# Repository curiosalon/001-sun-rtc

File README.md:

# NVRAM/IDPROM Replacement for M48T59Y Real Time Clock

This project intends to design a timing and register compatible module
to replace the now obsoleted M48T59Y realtime clock chip used in
the following Sun Microsystems computers:

| WORKSTATION SYSTEM | HOSTID   | COMPONENT | SUN PART    |
|:-------------------|:---------|:----------|:------------|
| **Sun Blade 100**  | 8xxxxxxx | 48T59     | f100-6889   |
| **Sun Blade 150**  | 83xxxxxx | 48T59     | f100-6889   |
| **Ultra 1**        | 80xxxxxx | 48T59     | 525-1430    |
| **Ultra 2**        | 80xxxxxx | 48T59     | 525-1417    |
| **Ultra 5/10**     | 8xxxxxxx | 48T59     | 525-1430    |
| **Ultra 30**       | 80xxxxxx | 48T59     | 525-1430    |
| **Ultra 60**       | 8xxxxxxx | 48T59     | 525-1430    |
| **Ultra 80**       | 8xxxxxxx | 48T59     | 525-1785    |

| WORKSTATION SYSTEM | HOSTID   | COMPONENT | SUN PART    |
|:-------------------|:---------|:----------|:------------|
| **E220R**          | 8xxxxxxx | 48T59     | 525-1430    |
| **E250**           | 83xxxxxx | 48T59     | 525-1726    |
| **E420R**          | 80xxxxxx | 48T59     | 525-1785    |
| **E450**           | 80xxxxxx | 48T59     | 525-1673    |
| **Ex000 Clock**    | 8xxxxxxx | 48T59     | f100-4007   |
| **Ex000 I/O**      | 80xxxxxx | 48T59     | f100-4007   |
| **Fx800 Sys Cont** | 8xxxxxxx | 48T59     | f100-4007   |
| **Ex900 Sys Cont** | 8xxxxxxx | 48T59     | 100-7822    |

| TELCO SYSTEM             | HOSTID   | COMPONENT | SUN PART    |
|:-------------------------|:---------|:----------|:------------|
| **Netra 120**            | ---      | 48T59     | 100-6889    |
| **Sun Fire V120**        | ---      | 48T59     | 100-6889    |
| **Netra AX1105**         | 83xxxxxx | 48T59     | ?           |
| **SPARCengine CP1400**   | 8xxxxxxx | 48T59     | 525-1803    |
| **Netra CP2140**         | 83xxxxxx | 48T59     | 100-5876    |
| **Netra CP2140**         | 83xxxxxx | 48T59     | 100-5893    |
| **Netra T1 AC200/DC200** | ---      | 48T59     | 100-6889    |

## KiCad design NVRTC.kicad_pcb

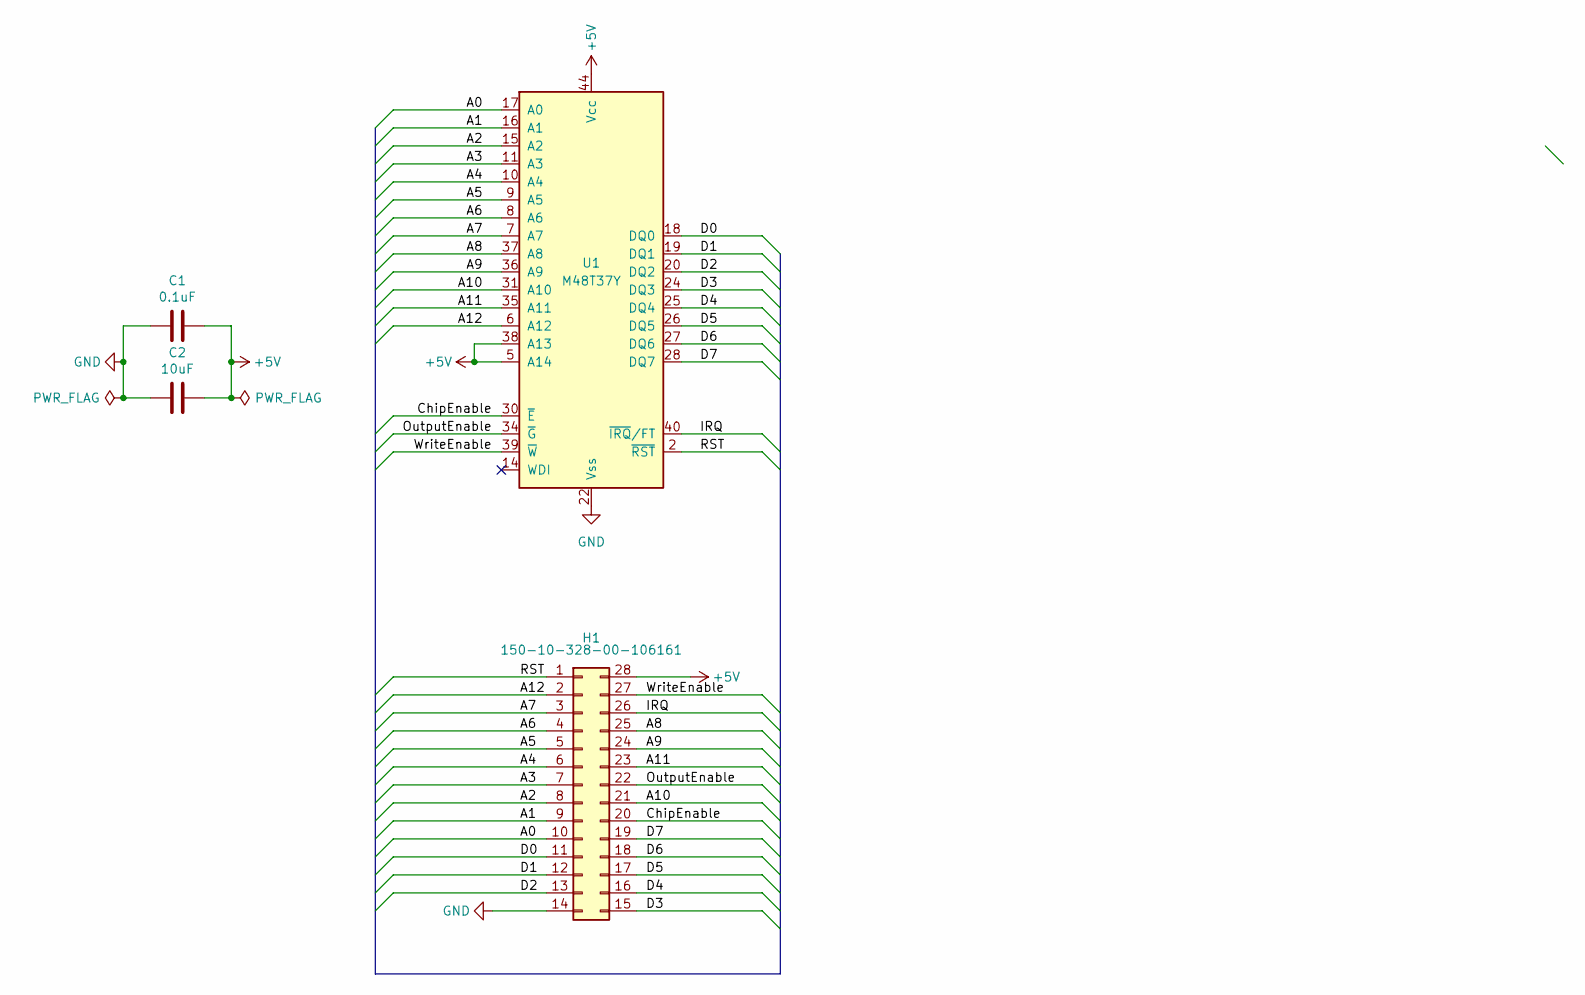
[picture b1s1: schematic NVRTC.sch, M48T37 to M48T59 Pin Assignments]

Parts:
C1: 0.1uF; C_0805_2012Metric_Pad1.18x1.45mm_HandSolder
C2: 10uF; C_0805_2012Metric_Pad1.18x1.45mm_HandSolder
H1: 150-10-328-00-106161; DIL28-M48T59Y
U1: M48T37Y; STM-SOH-44

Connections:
+5V: C1.1, C2.1, H1.28, U1.5 (A14), U1.38 (A13), U1.44 (Vcc)
/A0: H1.10, U1.17 (A0)
/A1: H1.9, U1.16 (A1)
/A2: H1.8, U1.15 (A2)
/A3: H1.7, U1.11 (A3)
/A4: H1.6, U1.10 (A4)
/A5: H1.5, U1.9 (A5)
/A6: H1.4, U1.8 (A6)
/A7: H1.3, U1.7 (A7)
/A8: H1.25, U1.37 (A8)
/A9: H1.24, U1.36 (A9)
/A10: H1.21, U1.31 (A10)
/A11: H1.23, U1.35 (A11)
/A12: H1.2, U1.6 (A12)
/ChipEnable: H1.20, U1.30 (~E)
/D0: H1.11, U1.18 (DQ0)
/D1: H1.12, U1.19 (DQ1)
/D2: H1.13, U1.20 (DQ2)
/D3: H1.15, U1.24 (DQ3)
/D4: H1.16, U1.25 (DQ4)
/D5: H1.17, U1.26 (DQ5)
/D6: H1.18, U1.27 (DQ6)
/D7: H1.19, U1.28 (DQ7)
/IRQ: H1.26, U1.40 (~IRQ~/FT)
/OutputEnable: H1.22, U1.34 (~G)
/RST: H1.1, U1.2 (~RST~)
/WriteEnable: H1.27, U1.39 (~W)
GND: C1.2, C2.2, H1.14, U1.22 (Vss)

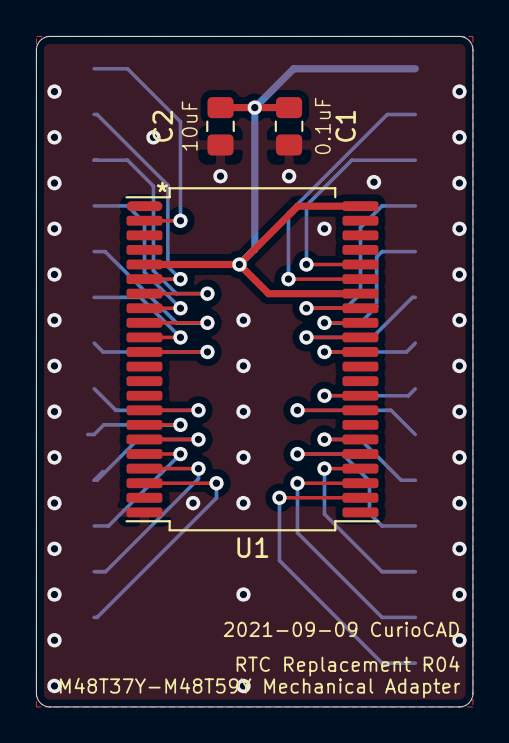
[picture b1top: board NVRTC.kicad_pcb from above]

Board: 2 copper layers, 24.2 x 37.2 mm, 4 parts (1 on the bottom side), 28 nets.

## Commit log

2021-09-03 Configure project in git
2021-09-03 Update gitignore
2021-09-11 Bump to Revision 4 Convert clock to M48T37 away from DS1554 Convert wiring to bus since all connections are labeled M48T37 Footprint is untested since manufacturer footprint is unavailable
2021-09-12 Rev 4
2021-09-12 Document compatible equipment
2021-09-12 Update README.md
    Not actually designing an IC right now
